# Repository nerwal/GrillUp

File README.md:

GrillUp
=======

Design files for the GrillUp project. 
Project logs, video, and general information is available at https://hackaday.io/project/2346

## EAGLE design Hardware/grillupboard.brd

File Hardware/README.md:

Hardware project files for GrillUp PCB, made in Eagle.

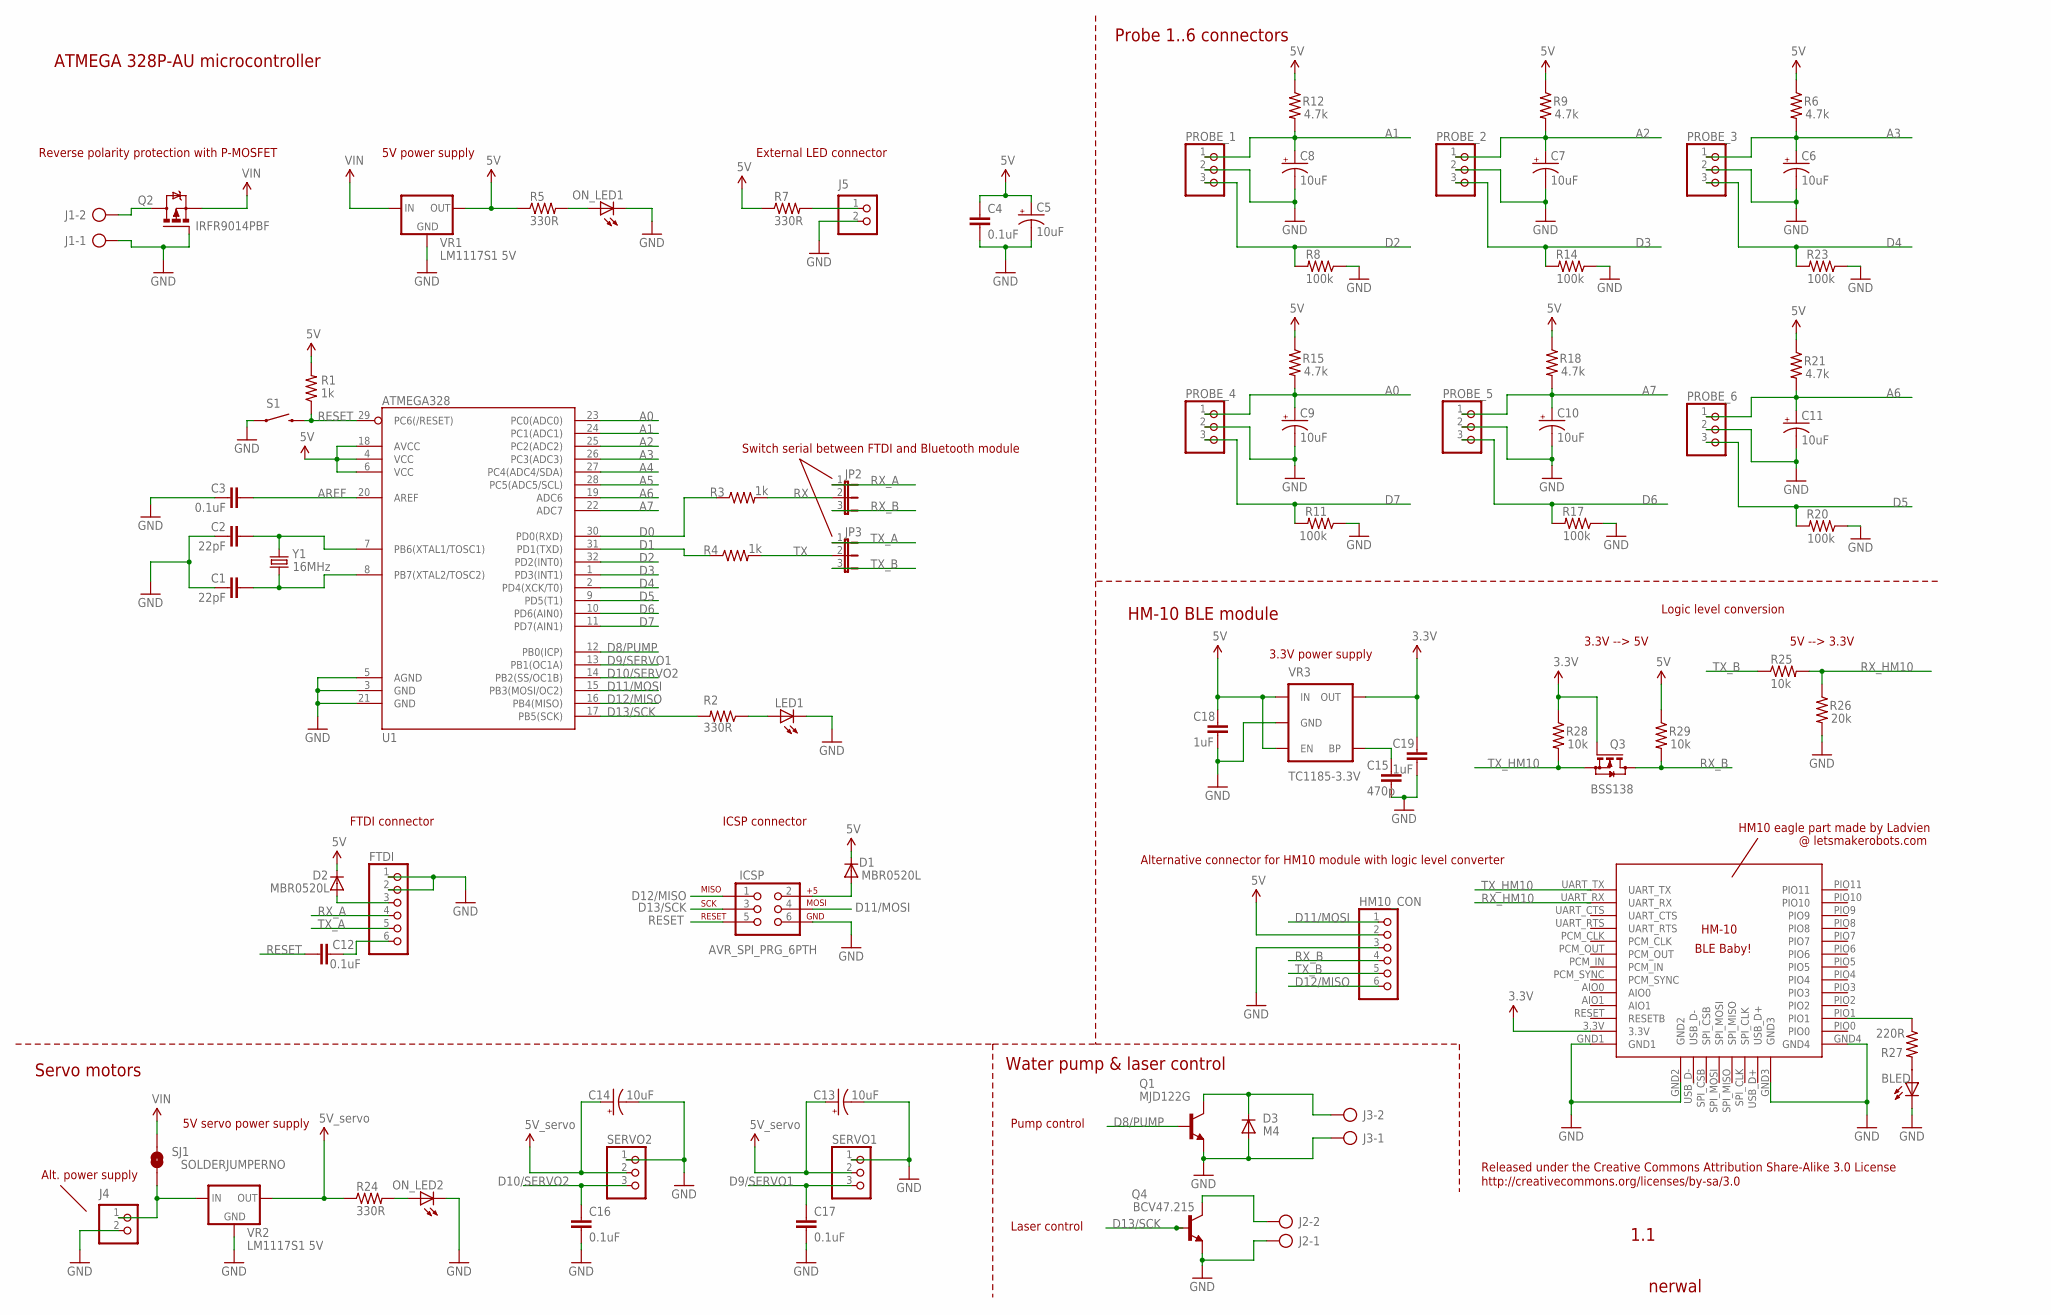
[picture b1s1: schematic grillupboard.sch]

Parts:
BLED: LED0603; LED-0603
C1, C2: 22pF; 0805
C3, C4, C12, C16, C17: 0.1uF; 0805
C5, C6, C7, C8, C9, C10, C11, C13, C14: 10uF; EIA3216
C15: 470p; 0805
C18, C19: 1uF; 0805
D1, D2: MBR0520L; SOD123
D3: M4; SMA-DIODE
FTDI: PINHD-1X6; 1X06
HM10: RANDOM_PARTS_BLE-HM-10
HM10_CON: PINHD-1X6; 1X06
ICSP: AVR_SPI_PRG_6PTH; 2X3
J1, J2, J3: AK500/2-H
J4, J5: PINHD-1X2; 1X02
JP2, JP3: JP2E; JP2
LED1: LED0603; LED-0603
ON_LED1, ON_LED2: LED0603; LED-0603
PROBE_1, PROBE_2, PROBE_3, PROBE_4, PROBE_5, PROBE_6: PINHD-1X3; 1X03
Q1: MJD122G; DPAK
Q2: IRFR9014PBF; D-PAK_TO252AA
Q3: BSS138; SOT23
Q4: BCV47.215; SOT23-BEC
R1, R3, R4: 1k; 0805
R2, R5, R7, R24: 330R; 0805
R6, R9, R12, R15, R18, R21: 4.7k; 0805
R8, R11, R14, R17, R20, R23: 100k; 0805
R25, R28, R29: 10k; 0805
R26: 20k; 0805
R27: 220R; 0805
S1: SWITCH-MOMENTARY-2-SMD-1101NE; TACTILE-SWITCH-1101NE
SERVO1, SERVO2: PINHD-1X3; 1X03
SJ1: SOLDERJUMPERNO; SJ_2S-NO
U1: ATMEGA328; TQFP32-08
VR1, VR2: LM1117S1 5V; SOT223
VR3: TC1185-3.3V; SOT23-5
Y1: 16MHz; HC49/S

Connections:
3.3V: C19.1, HM10.3.3V, Q3.1 (G), R28.1, VR3.5 (OUT)
5V: C4.1, C5.A (+), C18.1, D1.C, D2.C, HM10_CON.2, R1.2, R5.1, R6.1, R7.1, R9.1, R12.1, R15.1, R18.1, R21.1, R29.1, U1.4 (VCC), U1.6 (VCC), U1.18 (AVCC), VR1.2 (OUT), VR3.1 (IN), VR3.3 (EN)
A0: C9.A (+), PROBE_4.1, R15.2, U1.23 (PC0(ADC0))
A1: C8.A (+), PROBE_1.1, R12.2, U1.24 (PC1(ADC1))
A2: C7.A (+), PROBE_2.1, R9.2, U1.25 (PC2(ADC2))
A3: C6.A (+), PROBE_3.1, R6.2, U1.26 (PC3(ADC3))
A4: U1.27 (PC4(ADC4/SDA))
A5: U1.28 (PC5(ADC5/SCL))
A6: C11.A (+), PROBE_6.1, R21.2, U1.19 (ADC6)
A7: C10.A (+), PROBE_5.1, R18.2, U1.22 (ADC7)
AREF: C3.2, U1.20 (AREF)
D0: R3.1, U1.30 (PD0(RXD))
D1: R4.1, U1.31 (PD1(TXD))
D2: PROBE_1.3, R8.2, U1.32 (PD2(INT0))
D3: PROBE_2.3, R14.2, U1.1 (PD3(INT1))
D4: PROBE_3.3, R23.2, U1.2 (PD4(XCK/T0))
D5: PROBE_6.3, R20.2, U1.9 (PD5(T1))
D6: PROBE_5.3, R17.2, U1.10 (PD6(AIN0))
D7: PROBE_4.3, R11.2, U1.11 (PD7(AIN1))
D8/PUMP: Q1.1 (B), U1.12 (PB0(ICP))
D9/SERVO1: C17.1, SERVO1.3, U1.13 (PB1(OC1A))
D10/SERVO2: C16.1, SERVO2.3, U1.14 (PB2(SS/OC1B))
D11/MOSI: HM10_CON.1, ICSP.4, U1.15 (PB3(MOSI/OC2))
D12/MISO: HM10_CON.6, ICSP.1, U1.16 (PB4(MISO))
D13/SCK: ICSP.3, Q4.B, R2.2, U1.17 (PB5(SCK))
GND: BLED.C, C1.1, C2.1, C3.1, C4.2, C5.C (-), C6.C (-), C7.C (-), C8.C (-), C9.C (-), C10.C (-), C11.C (-), C13.C (-), C14.C (-), C15.2, C16.2, C17.2, C18.2, C19.2, D3.A, FTDI.1, FTDI.2, HM10.GND1, HM10.GND2, HM10.GND3, HM10.GND4, HM10_CON.3, ICSP.6, J1.1, J2.1, J3.1, J4.2, J5.2, LED1.C, ON_LED1.C, ON_LED2.C, PROBE_1.2, PROBE_2.2, PROBE_3.2, PROBE_4.2, PROBE_5.2, PROBE_6.2, Q1.3 (E), Q2.1 (G), Q4.E, R8.1, R11.1, R14.1, R17.1, R20.1, R23.1, R26.2, S1.P$1 (1), SERVO1.1, SERVO2.1, U1.3 (GND), U1.5 (AGND), U1.21 (GND), VR1.1 (GND), VR2.1 (GND), VR3.2 (GND)
unnamed: C2.2, U1.7 (PB6(XTAL1/TOSC1)), Y1.2
unnamed: C1.2, U1.8 (PB7(XTAL2/TOSC2)), Y1.1
unnamed: ON_LED1.A, R5.2
unnamed: D1.A, ICSP.2
unnamed: LED1.A, R2.1
unnamed: ON_LED2.A, R24.2
unnamed: D3.C, J3.2, Q1.4 (C)
unnamed: D2.A, FTDI.3
unnamed: J1.2, Q2.4 (D)
unnamed: J4.1, SJ1.1, VR2.3 (IN)
unnamed: C12.2, FTDI.6
unnamed: J2.2, Q4.C
unnamed: HM10.PIO1, R27.1
unnamed: BLED.A, R27.2
unnamed: C15.1, VR3.4 (BP)
unnamed: J5.1, R7.2
RESET: C12.1, ICSP.5, R1.1, S1.P$2 (2), U1.29 (PC6(/RESET))
RX: JP2.2, R3.2
RX_A: FTDI.4, JP2.1
RX_B: HM10_CON.4, JP2.3, Q3.3 (D), R29.2
RX_HM10: HM10.UART_RX, R25.2, R26.1
TX: JP3.2, R4.2
TX_A: FTDI.5, JP3.1
TX_B: HM10_CON.5, JP3.3, R25.1
TX_HM10: HM10.UART_TX, Q3.2 (S), R28.2
VCC: C13.A (+), C14.A (+), R24.1, SERVO1.2, SERVO2.2, VR2.2 (OUT)
VIN: Q2.3 (S), SJ1.2, VR1.3 (IN)

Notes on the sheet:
ICSP connector
FTDI connector
Pump control
5V servo power supply
Laser control
Alternative connector for HM10 module with logic level converter
nerwal
Probe 1..6 connectors
HM-10 BLE module
Water pump & laser control
Servo motors
ATMEGA 328P-AU microcontroller
Switch serial between FTDI and Bluetooth module
Logic level conversion
5V --> 3.3V
3.3V --> 5V
HM10 eagle part made by Ladvien
3.3V power supply
5V power supply
1.1
Reverse polarity protection with P-MOSFET
External LED connector
Alt. power supply
@ letsmakerobots.com
Released under the Creative Commons Attribution Share-Alike 3.0 License
http://creativecommons.org/licenses/by-sa/3.0

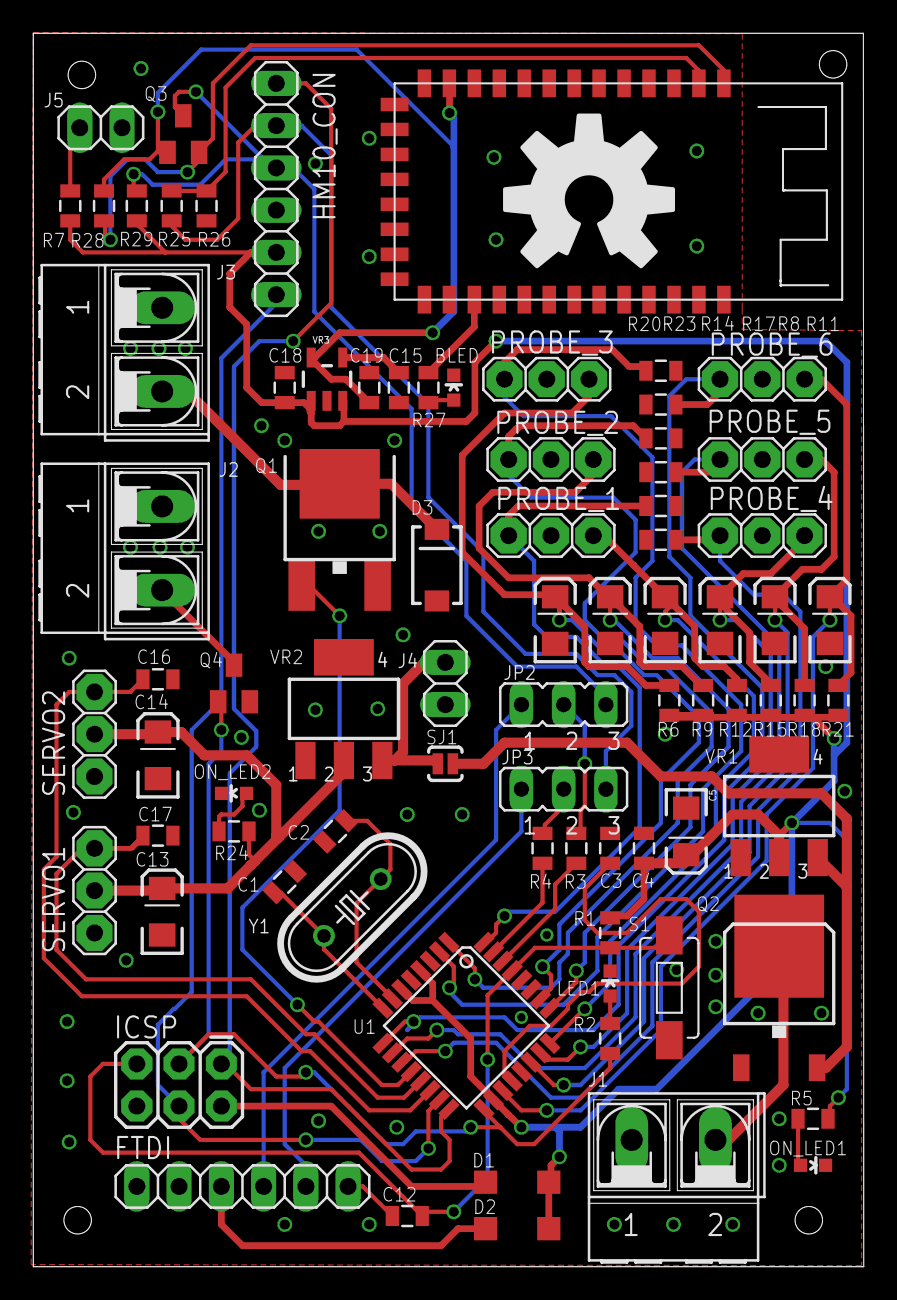
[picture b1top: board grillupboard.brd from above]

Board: 2 copper layers, 49.9 x 74.1 mm, 80 parts (0 on the bottom side), 51 nets.

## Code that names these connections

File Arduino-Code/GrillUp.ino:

/* GrillUp - remote grill temperature monitor
   uses Bluetooth 4.0 to communicate with Android app
   https://hackaday.io/project/2346
   Arduino Code
*/
#include <Servo.h> 
#include <Serial.h>

Servo servo1;
Servo servo2;

// pin configuration
byte Sensors[] = {A1, A2, A3, A0, A7, A6}; // analog pins that read temperature probe resistance
byte Probe_check[] = {2, 3, 4, 7, 6, 5}; // to check if temperature probe is connected
byte servo1_pin= 9; 
byte servo2_pin= 10;
byte pump_pin = 8;
byte laser_pin = 13;

// data arrays
int Coord[][2] = {{100,20},{100,20},{100,20},{100,20},{100,20},{100,20}}; // coordinates for each probe
int coord_temp[] = {0,100,80}; // temporary coordinates
int Temp_pairs[][2]={{0, 250},{7, 200},{10, 190},{25, 151},{51, 132},{69, 124},{150, 100},{208, 90},{250, 82},{328, 63},{420, 55},{445, 52},{555, 43},{570, 41},{616, 39},{671, 34},{774, 31},{950, 25},{973, 21},{1023, 1}};
byte temperature[6]; // temperature in Celcius degres
int Auto[]={0, 0, 0, 0, 0, 0}; // temperature limits for auto-cooling feature
int zone[]={55,145,70,120}; // vertical motor: from [0]-->[1], horizontal motor: [2]-->[3]

// available serial commands
char command;
char parameter0;
char parameter1;
char cool = 'A';
char coolXY = 'B';
char servo = 'C';
char auto_cooling = 'D';
char laser= 'E';

// counter variables
int interval = 1000; // time between temperature updates (miliseconds)
unsigned long start_time=0;
int duration=0; // actual millis() minus start time

void setup()
{
  Serial.begin(9600);
  // pin configuration
  pinMode(pump_pin, OUTPUT); 
  digitalWrite(pump_pin, LOW);
  pinMode(laser_pin, OUTPUT); 
  digitalWrite(laser_pin, LOW);

  for (int x = 0; x < 6; x++)  {
    pinMode(Sensors[x], INPUT);  
    pinMode(Probe_check[x], INPUT);  
  }  
  
  servo1.attach(servo1_pin);
  servo2.attach(servo2_pin);
  start_time=millis();
}

void loop(){
  
  duration=millis()-start_time;
  if(duration>interval){ // check temperature with intervals
    for(int x=0;x<6;x++){ 
      if(digitalRead(Probe_check[x])==LOW){ // checks whether the probe is connected
        int val= analogRead(Sensors[x]);
        temperature[x]=convertToCelcius(val);
      }else{
        temperature[x]=0x00;
      }
    }
    sendReadings(temperature);
    start_time=millis();
  }
  
  autoCooling(); // sprays probe if temperature exceeds treshold
  
  if(Serial.available() >= 3) {
    command = Serial.read();
    
    //dump the buffer if the first character was not a letter
    if(isalpha(command)){
    }
    if (!isalpha(command)){
      Serial.read(); // throw out the letter
      if ( Serial.available() < 2 ) {
        return;
      }
    }
  
  parameter0 = Serial.read(); // parameter 0
  parameter1 = Serial.read(); // parameter 1

  
  if (command == cool)  
  {
    // general cooling
    coolAll(zone);
  }
  else if (command == coolXY)
  {
    int target_int= parameter0 - '0'; // converting parameter 1 into int
    if(target_int<=5)
    {
      coolProbe(target_int);
    }
  }
  else if (command == servo)
  {
      int index= parameter0 - '0';
      if (index <= 5){
        if(index!=coord_temp[0]){
          coord_temp[0]=index;
          coord_temp[1]=Coord[index][0];
          coord_temp[2]=Coord[index][1];
        }
        switch(parameter1){
          case 'H':
            coord_temp[1]=coord_temp[1]+5; // add 5 degree to x-axis angle
            coord_temp[1]=constrain(coord_temp[1],0,180);
            break;
          case 'J':
            coord_temp[1]=coord_temp[1]-5; // subtract 5 degree from x-axis angle
            coord_temp[1]=constrain(coord_temp[1],0,180);
            break;
          case 'K':
            coord_temp[2]=coord_temp[2]+5; // add 5 degree to y-axis angle
            coord_temp[2]=constrain(coord_temp[2],0,180);
            break;
          case 'L':
            coord_temp[2]=coord_temp[2]-5; // subtract 5 degree from y-axis angle
            coord_temp[2]=constrain(coord_temp[2],0,180);
            break;
          case 'S':
            Coord[coord_temp[0]][0]=coord_temp[1]; // save coordinates
            Coord[coord_temp[0]][1]=coord_temp[2];
            laserControl(LOW); // turns off laser
            break;
        }
        setServo(coord_temp[1],coord_temp[2]); // set servos
      }
  }
  else if (command == laser)
  {
    switch(parameter0){
      case '0':
        laserControl(LOW);
        break;
      case '1':
        laserControl(HIGH);
        break;
    }
  }
  else if (command == auto_cooling)
  {
    // auto-cooling routine
    int index= parameter0 - '0';
    if (index <= 5){
      int val=(int)parameter1;
      Auto[index]=val;
    }
  } 
  command=0;
  parameter0=0;
  parameter1=0;
}
}

byte convertToCelcius(int reading){
  // converts reading from analog input to celcius degree
  int value=constrain(reading,0,1024);
  int lower_index=0;
  int upper_index=0;
  int num_rows = sizeof(Temp_pairs)/sizeof(Temp_pairs[0]);
  for (int x=1; x<num_rows; x++){
    if(value>=Temp_pairs[x][0]){
      lower_index=x;
    } 
  }
  upper_index=lower_index+1;
  int progress=100*(value-Temp_pairs[lower_index][0])/(Temp_pairs[upper_index][0]-Temp_pairs[lower_index][0]); // percentrage of progress 
  float temp_val=Temp_pairs[lower_index][1]+progress*((float)(Temp_pairs[upper_index][1]-Temp_pairs[lower_index][1])/100);
  byte temp=(byte)temp_val;
  return temp;
}

void coolAll(int xy[]){
  int change=5;
  for(int a=0;a<4;a++){
    xy[a]=constrain(xy[a],0,180);
  }
  int rangeX=xy[1]-xy[0];
  int rangeY=xy[3]-xy[2];
  if (rangeX<change){
    xy[1]=xy[0]+change;
  }
  if (rangeY<change){
    xy[3]=xy[2]+change;
  }
  digitalWrite(pump_pin, HIGH);
  delay(100);
  for(int x=xy[0];x<xy[1];x=x+change){
    servo1.write(x); 
    for(int y=xy[2];y<xy[3];y=y+change){ 
      servo2.write(y);
      delay(30);
    }
  }
  digitalWrite(pump_pin, LOW);  
}

void sendReadings(byte temperature[]){
  // sends temperature
  Serial.write(temperature[0]);
  Serial.write(temperature[1]);
  Serial.write(temperature[2]);
  Serial.write(temperature[3]);
  Serial.write(temperature[4]);
  Serial.write(temperature[5]);
}

void coolProbe(int target_probe){
  // sets servos on XY position, and turns pump on for set ms
  setServo(Coord[target_probe][0],Coord[target_probe][1]);
  delay(700);
  digitalWrite(pump_pin, HIGH);
  delay(1000);
  digitalWrite(pump_pin, LOW);
}

void autoCooling(){
  // turns on cooling if temperature excels set threshold
  for(int x=0; x<6; x++){
    if(Auto[x]!=0){
      if(temperature[x]>Auto[x]){
        coolProbe(x);
      }
    }
  }
}

void setServo(int x, int y){
  // sets servo to x,y coordinates
  int x_val= constrain(x, 0, 180);
  int y_val= constrain(y, 0, 180);
  servo1.write(x_val); 
  delay(10);
  servo2.write(y_val);
  delay(10);
}

void laserControl(boolean state){
  // turns on/off laser pointer
  digitalWrite(laser_pin, state);
}

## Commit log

2014-08-20 Create GrillUp.ino
    Main arduino code
2014-08-20 Eagle files uploaded

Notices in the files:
parts and their libraries:
SparkFun-DigitalIC: Licensing: CC v3.0 Share-Alike You are welcome to use this library for commercial purposes.
